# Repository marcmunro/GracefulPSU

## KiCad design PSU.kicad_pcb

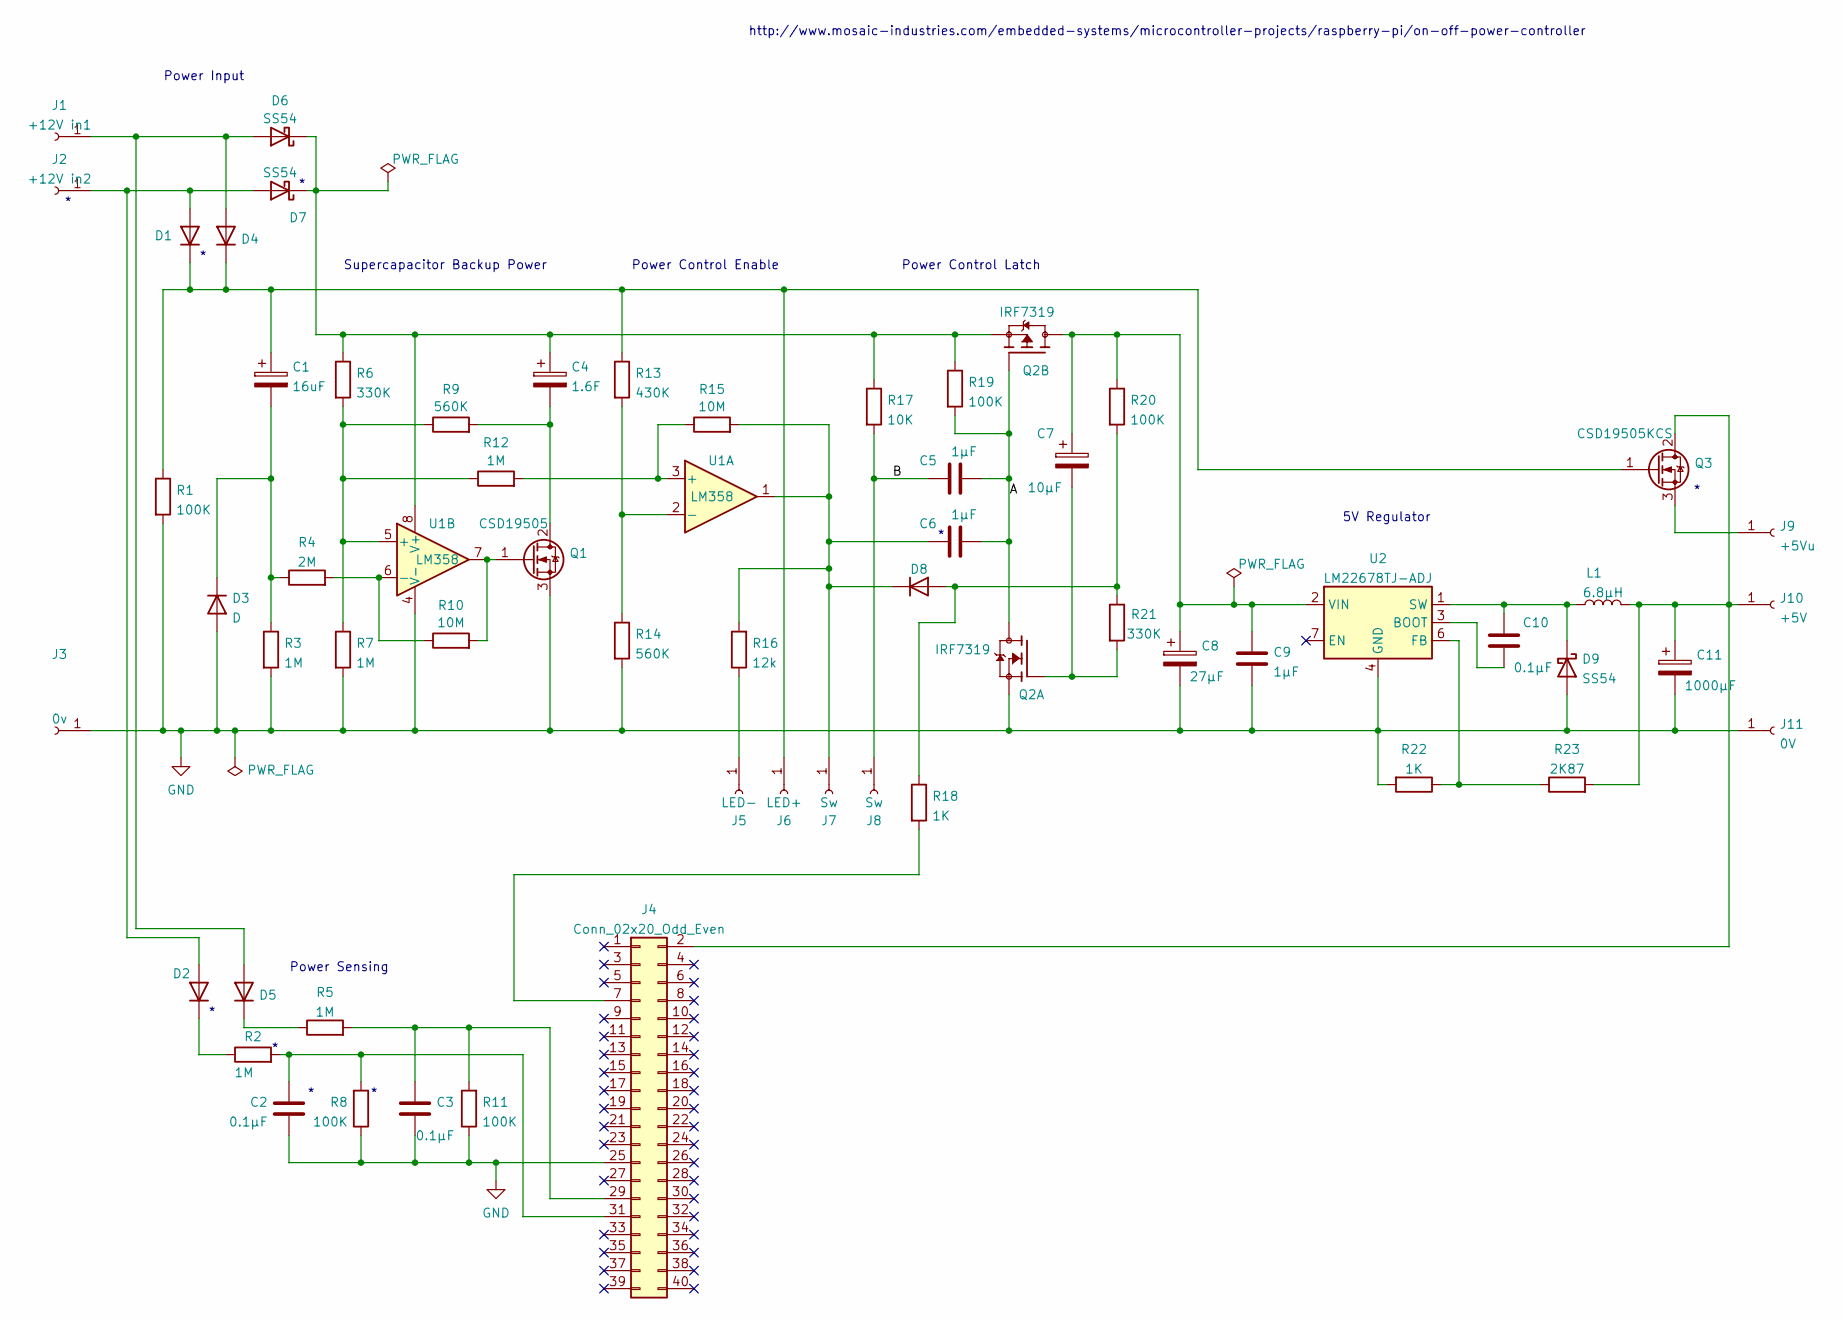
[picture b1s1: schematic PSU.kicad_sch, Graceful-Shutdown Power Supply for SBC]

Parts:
C1: 16uF; CP_Axial_L18.0mm_D6.5mm_P25.00mm_Horizontal
C2, C3, C10: 0.1μF; C_Disc_D5.0mm_W2.5mm_P2.50mm
C4: 1.6F; SuperCapacitor Module
C5, C6, C9: 1μF; C_Disc_D7.5mm_W2.5mm_P5.00mm
C7: 10μF; CP_Radial_D5.0mm_P2.00mm
C8: 27μF; CP_Radial_D5.0mm_P2.00mm
C11: 1000μF; CP_Radial_D8.0mm_P2.50mm
D1, D2, D3, D4, D5, D8: D; D_A-405_P7.62mm_Horizontal
D6, D7, D9: SS54; DO-214AC
J1: +12V in1; SolderConnector
J2: +12V in2; SolderConnector
J3: 0v; SolderConnector
J4: Conn_02x20_Odd_Even; PinHeader_2x20_P2.54mm_Vertical
J5: LED-; SolderConnector
J6: LED+; SolderConnector
J7, J8: Sw; SolderConnector
J9: +5Vu; SolderConnector
J10: +5V; SolderConnector
J11: 0V; SolderConnector
L1: 6.8μH; L_Bourns-SRU1028_10.0x10.0mm
Q1: CSD19505; TO-220-3_Vertical
Q2: IRF7319; SOIC127P600X175-8N
Q3: CSD19505KCS; TO-220-3_Vertical
R1, R8, R11, R19, R20: 100K; R_Axial_DIN0207_L6.3mm_D2.5mm_P10.16mm_Horizontal
R2, R3, R5, R7, R12: 1M; R_Axial_DIN0207_L6.3mm_D2.5mm_P10.16mm_Horizontal
R4: 2M; R_Axial_DIN0207_L6.3mm_D2.5mm_P10.16mm_Horizontal
R6, R21: 330K; R_Axial_DIN0207_L6.3mm_D2.5mm_P10.16mm_Horizontal
R9, R14: 560K; R_Axial_DIN0207_L6.3mm_D2.5mm_P10.16mm_Horizontal
R10, R15: 10M; R_Axial_DIN0207_L6.3mm_D2.5mm_P10.16mm_Horizontal
R13: 430K; R_Axial_DIN0207_L6.3mm_D2.5mm_P10.16mm_Horizontal
R16: 12k; R_Axial_DIN0207_L6.3mm_D2.5mm_P10.16mm_Horizontal
R17: 10K; R_Axial_DIN0207_L6.3mm_D2.5mm_P10.16mm_Horizontal
R18, R22: 1K; R_Axial_DIN0207_L6.3mm_D2.5mm_P10.16mm_Horizontal
R23: 2K87; R_Axial_DIN0207_L6.3mm_D2.5mm_P10.16mm_Horizontal
U1: LM358; DIP-8_W7.62mm
U2: LM22678TJ-ADJ; TO-263-7_TabPin8

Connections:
/A: C5.1, C6.1, Q2.4 (G2), Q2.7 (D1), Q2.8 (D1), R19.2
/B: C5.2, J8.1, R17.2
GND: C2.1, C3.2, C8.2, C9.2, C11.2, D3.2 (A), D9.2 (A), J3.1, J4.25, J11.1, Q1.3 (S), Q2.1 (S1), R1.2, R3.2, R7.2, R8.1, R11.1, R14.2, R22.2, U1.4 (V-), U2.4 (GND), U2.8 (GND)
unnamed: C1.1, D1.1 (K), D4.1 (K), J6.1, Q3.1 (G), R1.1, R13.1
unnamed: C1.2, D3.1 (K), R3.1, R4.1
unnamed: C2.2, J4.31, R2.2, R8.2
unnamed: C3.1, J4.29, R5.2, R11.2
unnamed: C4.1, D6.1 (K), D7.1 (K), Q2.3 (S2), R6.1, R17.1, R19.1, U1.8 (V+)
unnamed: C4.2, Q1.2 (D), R9.2
unnamed: C6.2, D8.1 (K), J7.1, R15.2, R16.2, U1.1
unnamed: C7.1, C8.1, C9.1, Q2.5 (D2), Q2.6 (D2), R20.1, U2.2 (VIN)
unnamed: C7.2, Q2.2 (G1), R21.2
unnamed: C10.1, U2.3 (BOOT)
unnamed: C10.2, D9.1 (K), L1.1, U2.1 (SW)
unnamed: C11.1, J4.2, J10.1, L1.2, Q3.2 (D), R23.2
unnamed: D1.2 (A), D2.2 (A), D7.2 (A), J2.1
unnamed: D2.1 (K), R2.1
unnamed: D4.2 (A), D5.2 (A), D6.2 (A), J1.1
unnamed: D5.1 (K), R5.1
unnamed: D8.2 (A), R18.1, R20.2, R21.1
unnamed: J4.7, R18.2
unnamed: J5.1, R16.1
unnamed: J9.1, Q3.3 (S)
unnamed: Q1.1 (G), R10.2, U1.7
unnamed: R4.2, R10.1, U1.6 (-)
unnamed: R6.2, R7.1, R9.1, R12.1, U1.5 (+)
unnamed: R12.2, R15.1, U1.3 (+)
unnamed: R13.2, R14.1, U1.2 (-)
unnamed: R22.1, R23.1, U2.6 (FB)

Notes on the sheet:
http://www.mosaic-industries.com/embedded-systems/microcontroller-projects/raspberry-pi/on-off-power-controller
Power Control Latch
Supercapacitor Backup Power
5V Regulator
Power Input
Power Control Enable
Power Sensing

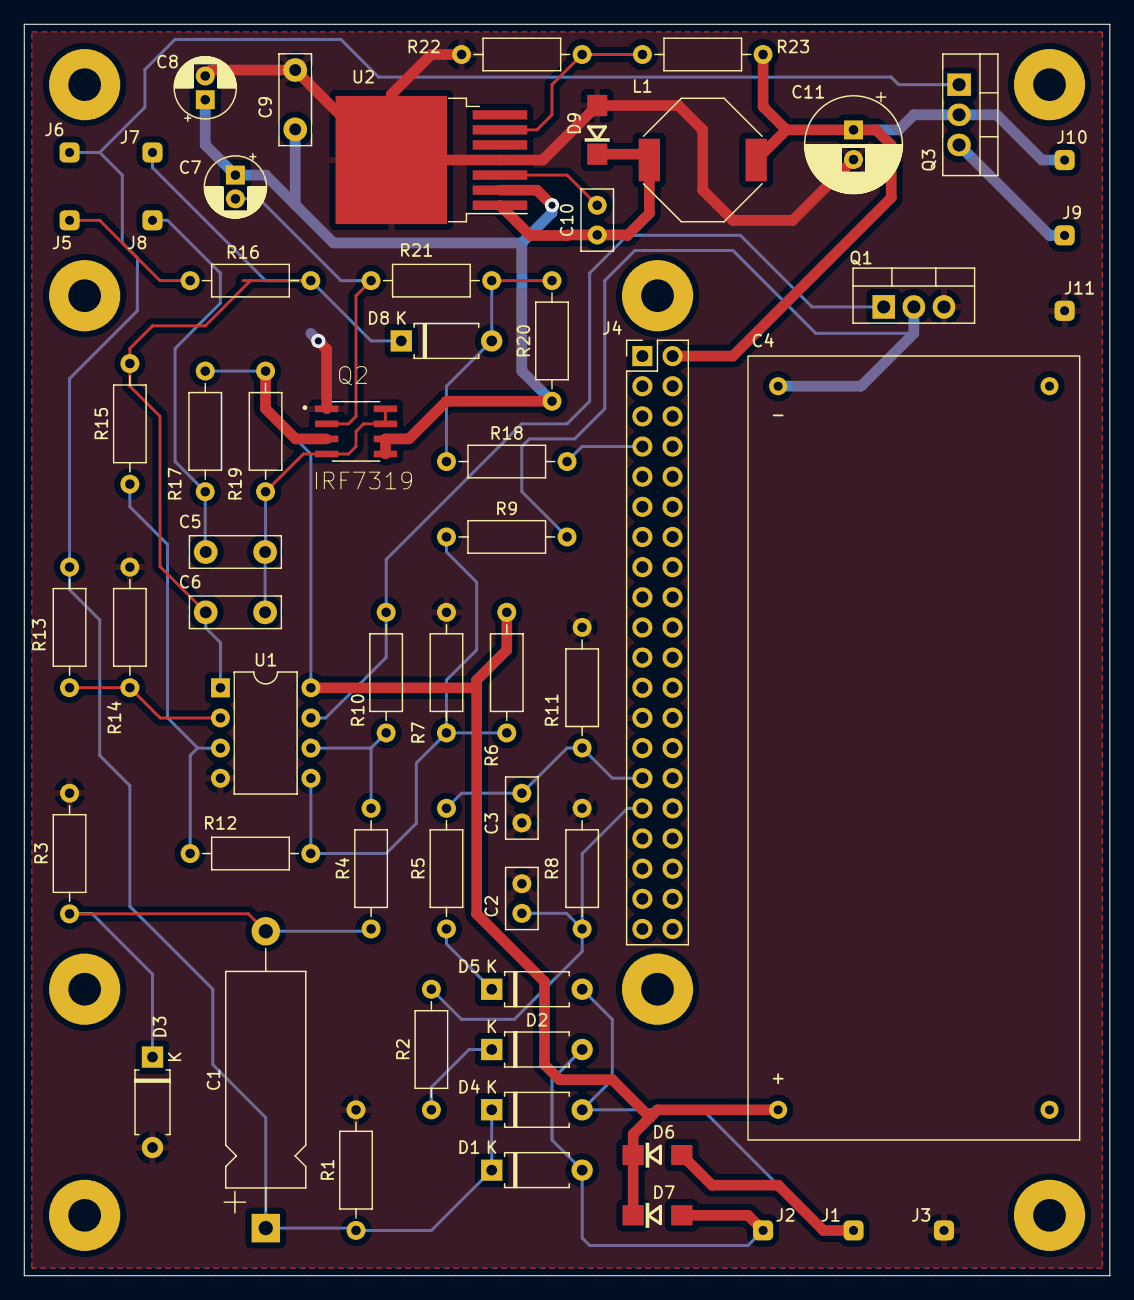
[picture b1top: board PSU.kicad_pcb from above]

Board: 2 copper layers, 91.4 x 105.4 mm, 60 parts (0 on the bottom side), 29 nets.

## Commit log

2022-03-26 Initial commit to git.
2022-03-26 Initial .gitignore file added.
2022-03-26 Prep for release to github
2022-03-28 Updates prior to pcb order.
2022-03-28 Moved kicad files into dedicated subdirectory
2022-03-28 Updated docs, created README.
2022-03-28 Removed old psu.txt file
2022-03-28 Added license file, tweaked README.
2022-03-28 Tweak to README for links
2022-03-28 Trying to get README links working
2022-03-28 More link tweaks
2022-03-28 Documentation updates. Fix to simualation.
2022-11-05 Still setting up...
